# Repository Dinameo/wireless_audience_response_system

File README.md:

# Hệ thống trắc nghiệm tương tác sử dụng BLE và Wi-Fi

## Giới thiệu dự án

Dự án xây dựng hệ thống trắc nghiệm tương tác hỗ trợ tổ chức và theo dõi bài kiểm tra trong lớp học. Thay vì trả lời trực tiếp trên điện thoại hoặc máy tính, sinh viên có thể sử dụng thiết bị IoT với các nút A/B/C/D và SUBMIT để chọn rồi gửi đáp án. Giảng viên quản lý lớp học, danh sách sinh viên, câu hỏi và lượt thi trên giao diện web.

Hệ thống kết nối thiết bị theo hai cách: bo nRF52840 gửi dữ liệu BLE qua gateway chạy trên máy tính; bo ESP32 kết nối Wi-Fi và gửi dữ liệu đến API. Backend FastAPI xác thực thiết bị, tiếp nhận đáp án, lưu dữ liệu vào MySQL và cập nhật trạng thái bài thi để giảng viên theo dõi. Sau khi kết thúc, giảng viên có thể xem kết quả, thống kê và xuất bảng điểm.

Mục tiêu của dự án là kết hợp phần cứng IoT, giao tiếp không dây và phần mềm quản lý thành một quy trình trả lời trắc nghiệm liền mạch: từ tạo bài thi, ghép thiết bị với sinh viên, mở câu hỏi, nhận đáp án đến tổng hợp kết quả.

## Thành viên

| Họ và tên | MSSV |
|---|---:|
| Vũ Phạm Đức Văn | 23134064 |
| Phạm Đức Huy | 23134026 |
| Nguyễn Thiện Nhân | 23134041 |

Đề tài môn IoT, Khoa Cơ khí – Bộ môn Cơ điện tử, Trường Đại học Công nghệ Kỹ thuật TP. Hồ Chí Minh. Giảng viên hướng dẫn: TS. Bùi Hà Đức.

## Kiến trúc hệ thống

Hệ thống có hai lựa chọn thiết bị trả lời. nRF52840 gửi dữ liệu qua BLE tới gateway Python chạy trên laptop; ESP32 kết nối Wi-Fi và gọi API trực tiếp. Cả hai đường truyền đều đi tới FastAPI và MySQL. Trình duyệt giảng viên làm việc với web/API và nhận cập nhật qua WebSocket.

*nRF52840 dùng BLE gateway; ESP32 dùng Wi-Fi/HTTP trực tiếp tới server.*

## Chức năng chính

- Quản lý tài khoản giảng viên, môn học, lớp và danh sách sinh viên.
- Tạo bài thi, nhập câu hỏi từ DOCX/PDF có lớp văn bản và nhập danh sách từ Excel.
- Ghép thiết bị với sinh viên ở đầu mỗi lượt thi; danh sách ghép trong lượt thi là nguồn xác định chủ sở hữu đáp án.
- Trình chiếu câu hỏi, theo dõi trạng thái thiết bị, mở câu tiếp theo hoặc kết thúc bài thi.
- Từ chối đáp án của câu đã đóng, đáp án gửi trễ, nộp trùng hoặc thiết bị không thuộc lượt thi.
- Chấm điểm tối đa 10, xem thống kê và xuất bảng điểm cùng chi tiết câu trả lời ra Excel.

Theo báo cáo, cơ sở dữ liệu MySQL có 19 bảng cho tài khoản giảng viên, lớp/môn, sinh viên, lượt thi, câu hỏi, thiết bị, trạng thái kết nối và đáp án. Mỗi lượt thi chốt ghép thiết bị riêng; server ngăn dùng một thiết bị cho nhiều sinh viên trong cùng lượt và ngăn nộp lặp cho cùng câu.

## Luồng thiết bị nRF52840

Thiết bị có các nút A/B/C/D, nút SUBMIT, LED kết nối và LED gửi. Thiết bị quảng bá BLE; gateway nhận mã ID rồi hỏi server để xác thực. Khi server chấp nhận, gateway gửi ACCEPT. Lúc giảng viên mở câu, gateway gửi NEXT; người học chọn đáp án rồi nhấn SUBMIT để gửi ANS:X. Sau khi server lưu đáp án thành công, gateway gửi ACK. ACK xác nhận đã lưu, không báo đáp án đúng hay sai.

Mã firmware và mô tả state machine ở [NRF52840_Quiz_Remote_src/main/main.ino](NRF52840_Quiz_Remote_src/main/main.ino) và [README luồng firmware](NRF52840_Quiz_Remote_src/main/README.md). Mã gateway BLE cần chạy riêng trên máy có Bluetooth; gateway không nằm trong các tệp hiện có của repository.

## Giao diện web

Web cung cấp trang đăng nhập giảng viên và các chức năng quản lý lớp, thiết bị, bài thi và kết quả. Web và MySQL được triển khai bằng Docker Compose; FastAPI xử lý API và dữ liệu bài thi.

Xem cách chạy và cấu hình trong [web/README.md](web/README.md).

## Cấu trúc repository

- `web/`: giao diện giảng viên, FastAPI, API và cấu hình Docker Compose.
- `NRF52840_Quiz_Remote_src/main/`: firmware BLE cho thiết bị nRF52840 và tài liệu luồng hoạt động.
- `NRF52840_Quiz_Remote/`: sơ đồ nguyên lý, PCB KiCad và Gerber.
- `Case/`: các tệp thiết kế và STL liên quan đến vỏ thiết bị.
- `docs/images/`: ảnh kiến trúc, giao diện, luồng BLE và PCB trích từ báo cáo.

## Phần cứng

PCB nRF52840 được thiết kế hai lớp, có các đầu vào nút nhấn, hai LED trạng thái và LED nguồn. Báo cáo ghi kích thước thiết kế 66 × 152 mm, các nút chọn A/B/C/D và SUBMIT, cùng các thành phần nguồn và reset. Ảnh bên dưới đối chiếu mô hình PCB với ảnh bo đã gia công; ảnh chỉ ghi nhận một phần linh kiện đã lắp, không thay cho phép thử điện.

Ảnh đường mạch hai lớp F.Cu/B.Cu:

Báo cáo có mô tả quy trình thiết kế vỏ và một ảnh chi tiết vỏ in. Tuy nhiên báo cáo cũng nêu chưa có tệp SolidWorks/STL và chưa ghi nhận kiểm tra lắp ghép hoàn chỉnh; vì vậy phần vỏ vẫn cần được xác nhận thêm.

## Kiểm thử và giới hạn

Báo cáo ghi nhận một lượt thử nRF từ thao tác chọn C trên Serial đến ANS:C, nhận ACK và lưu lựa chọn C vào database. Báo cáo chưa có số liệu về độ trễ, tỷ lệ mất gói BLE hoặc kiểm thử tải với nhiều thiết bị cùng lúc.

Các lưu ý bảo mật được nêu trong báo cáo: BLE chưa có cơ chế chống giả mạo mạnh; ESP32 dùng HTTP trong mạng LAN và token thiết bị phải được giữ kín. Không đưa thông tin xác thực vào firmware công khai hoặc triển khai API trực tiếp lên Internet nếu chưa bổ sung bảo vệ phù hợp.

## Tài liệu

- [Báo cáo dự án (DOCX)](https://docs.google.com/document/d/1qnYOhXeeTpFeyJ0GafD6C87CJyP0sUIl/edit)
- [README hướng dẫn web](web/README.md)
- [README luồng firmware nRF52840](NRF52840_Quiz_Remote_src/main/README.md)

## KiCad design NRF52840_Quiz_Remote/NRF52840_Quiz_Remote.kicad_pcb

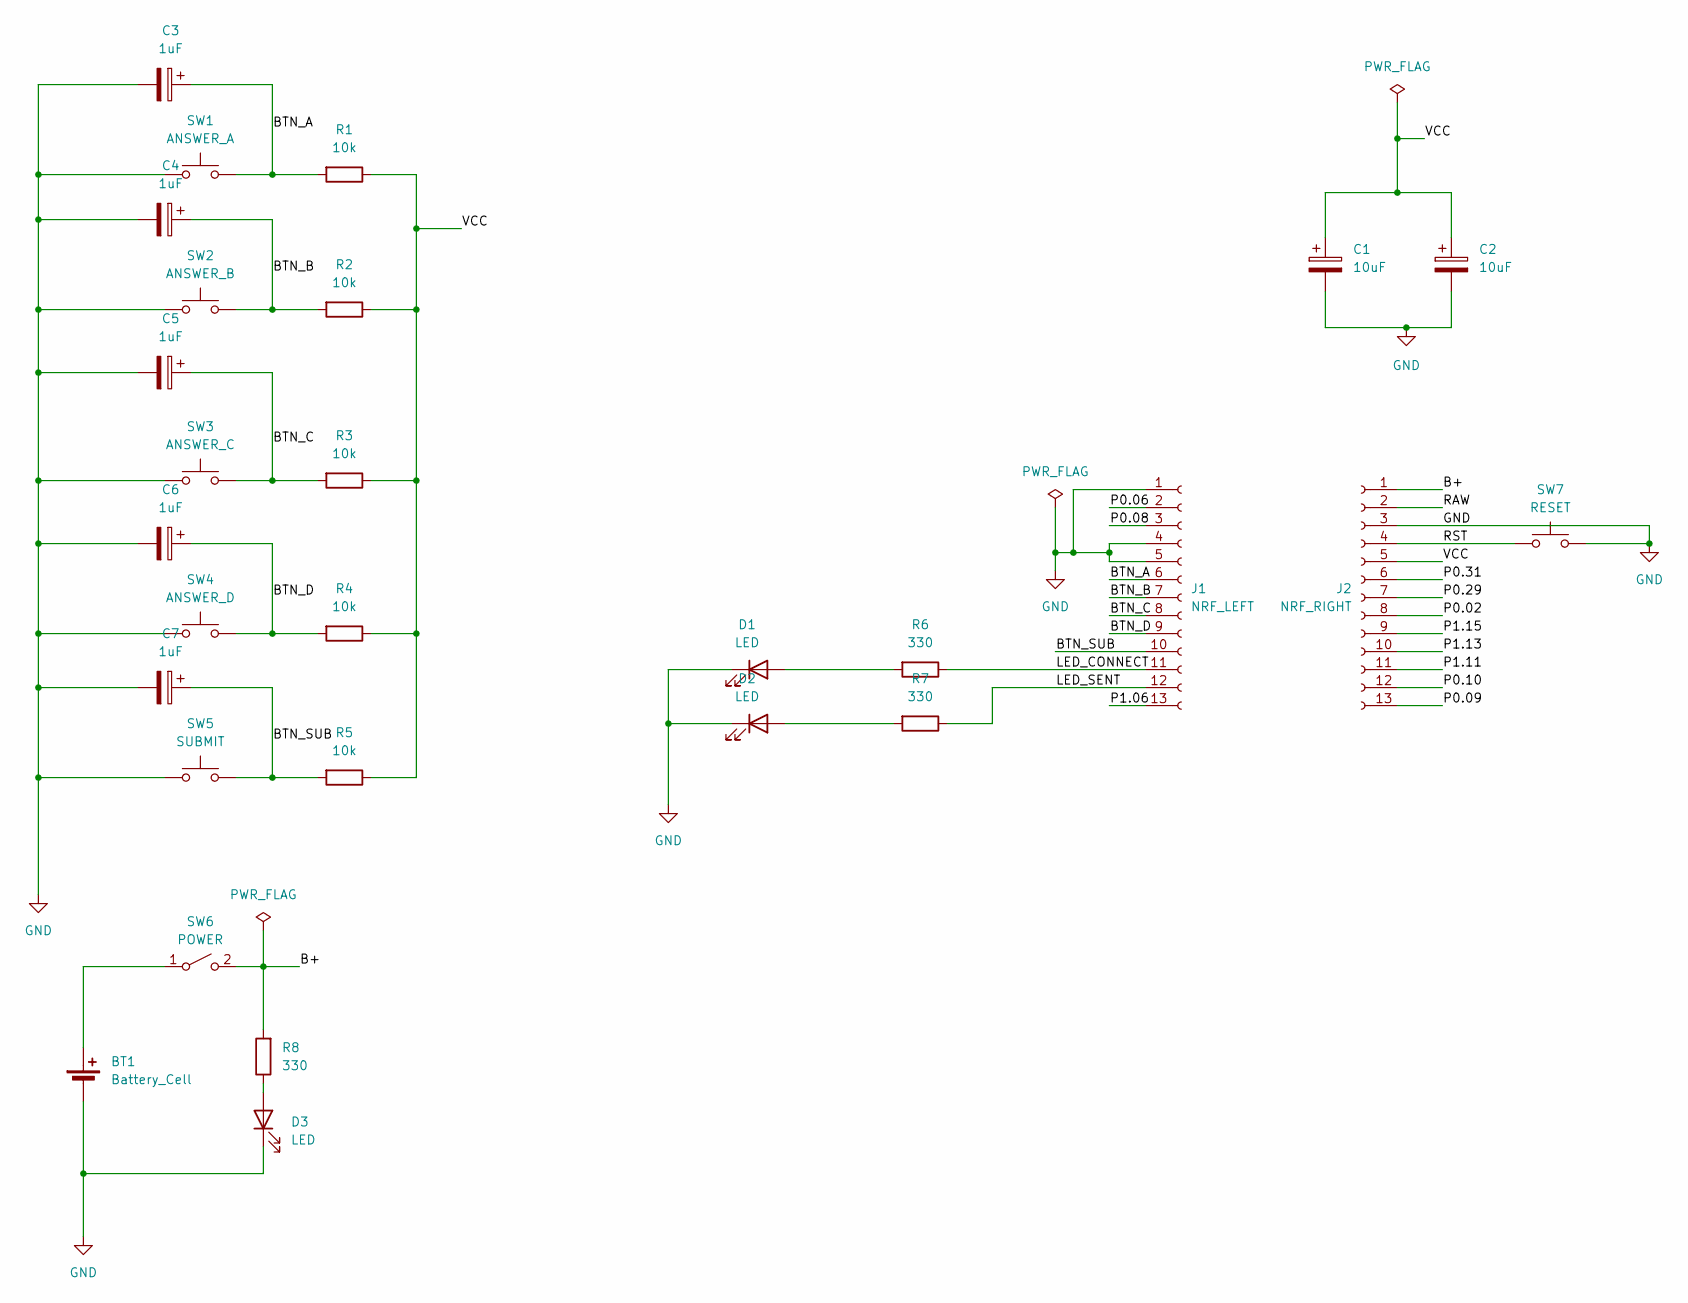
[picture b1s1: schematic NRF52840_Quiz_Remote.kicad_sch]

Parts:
BT1: Battery_Cell; Battery_Panasonic_CR2032-HFN_Horizontal_CircularHoles
C1, C2: 10uF; CP_Radial_D4.0mm_P2.00mm
C3, C4, C5, C6, C7: 1uF; CP_Radial_D5.0mm_P2.00mm
D1, D2, D3: LED; LED_D5.0mm
J1: NRF_LEFT; PinSocket_1x13_P2.54mm_Vertical
J2: NRF_RIGHT; PinSocket_1x13_P2.54mm_Vertical
R1, R2, R3, R4, R5: 10k; R_Axial_DIN0207_L6.3mm_D2.5mm_P7.62mm_Horizontal
R6, R7, R8: 330; R_Axial_DIN0207_L6.3mm_D2.5mm_P7.62mm_Horizontal
SW1: ANSWER_A; SW_PUSH_6mm_H4.3mm
SW2: ANSWER_B; SW_PUSH_6mm_H4.3mm
SW3: ANSWER_C; SW_PUSH_6mm_H4.3mm
SW4: ANSWER_D; SW_PUSH_6mm_H4.3mm
SW5: SUBMIT; SW_PUSH_6mm_H4.3mm
SW6: POWER; SS12D10_SPDT_v1
SW7: RESET; SW_PUSH_6mm_H4.3mm

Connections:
/B+: J2.1, R8.2, SW6.2 (B)
/BTN_A: C3.1, J1.6, R1.2, SW1.2
/BTN_B: C4.1, J1.7, R2.2, SW2.2
/BTN_C: C5.1, J1.8, R3.2, SW3.2
/BTN_D: C6.1, J1.9, R4.2, SW4.2
/BTN_SUB: C7.1, J1.10, R5.2, SW5.2
/LED_CONNECT: J1.11, R6.1
/LED_SENT: J1.12, R7.1
/P0.02: J2.8
/P0.06: J1.2
/P0.08: J1.3
/P0.09: J2.13
/P0.10: J2.12
/P0.29: J2.7
/P0.31: J2.6
/P1.06: J1.13
/P1.11: J2.11
/P1.13: J2.10
/P1.15: J2.9
/RAW: J2.2
/RST: J2.4, SW7.1
/VCC: C1.1, C2.1, J2.5, R1.1, R2.1, R3.1, R4.1, R5.1
GND: BT1.2 (-), C1.2, C2.2, C3.2, C4.2, C5.2, C6.2, C7.2, D1.1 (K), D2.1 (K), D3.1 (K), J1.1, J1.4, J1.5, J2.3, SW1.1, SW2.1, SW3.1, SW4.1, SW5.1, SW7.2
unnamed: BT1.1 (+), SW6.1 (A)
unnamed: D1.2 (A), R6.2
unnamed: D2.2 (A), R7.2
unnamed: D3.2 (A), R8.1

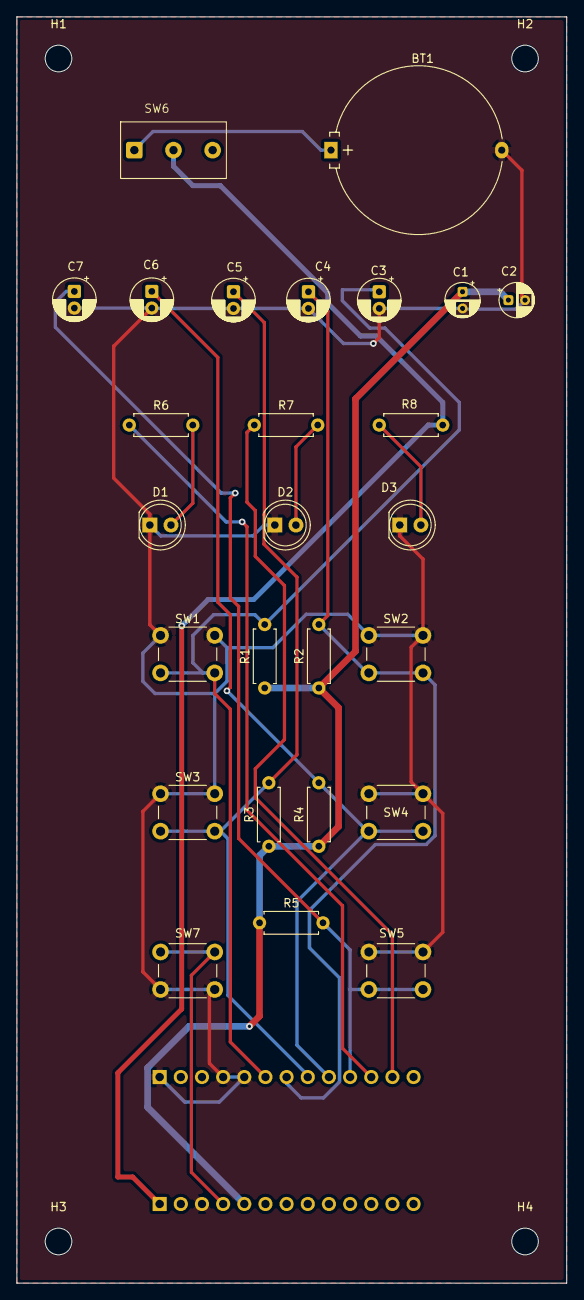
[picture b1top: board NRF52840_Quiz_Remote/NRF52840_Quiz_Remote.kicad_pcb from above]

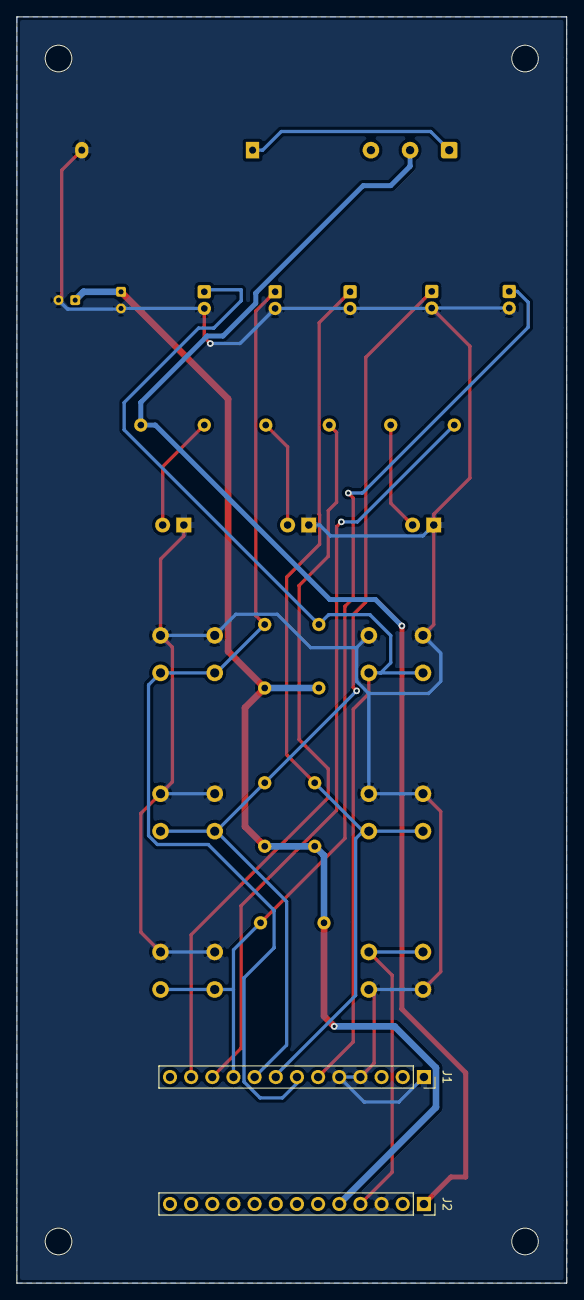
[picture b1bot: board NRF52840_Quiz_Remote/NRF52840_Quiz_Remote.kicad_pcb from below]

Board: 2 copper layers, 66.0 x 152.0 mm, 32 parts (2 on the bottom side), 15 nets.

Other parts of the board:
H1, H2, H3, H4: MountingHole_3.2mm_M3

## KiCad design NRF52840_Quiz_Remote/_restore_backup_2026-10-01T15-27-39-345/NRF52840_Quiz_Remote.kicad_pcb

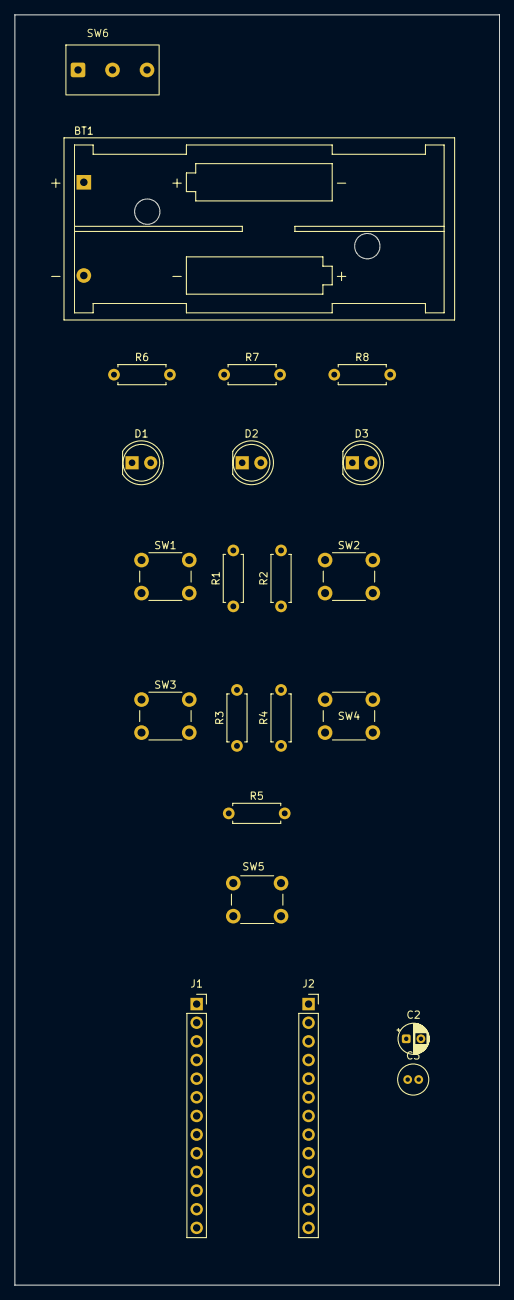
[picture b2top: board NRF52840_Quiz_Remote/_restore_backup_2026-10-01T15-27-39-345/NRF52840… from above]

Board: 2 copper layers, 66.0 x 173.0 mm, 22 parts (0 on the bottom side), 15 nets, no tracks yet.

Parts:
BT1: Battery; BatteryHolder_Keystone_2468_2xAAA
C2: 10uF; CP_Radial_D4.0mm_P2.00mm
C3: 100nF; C_Radial_D4.0mm_H5.0mm_P1.50mm
D1, D2, D3: LED; LED_D5.0mm
J1: NRF_LEFT; PinSocket_1x13_P2.54mm_Vertical
J2: NRF_RIGHT; PinSocket_1x13_P2.54mm_Vertical
R1, R2, R3, R4, R5: 10k; R_Axial_DIN0207_L6.3mm_D2.5mm_P7.62mm_Horizontal
R6, R7, R8: 330; R_Axial_DIN0207_L6.3mm_D2.5mm_P7.62mm_Horizontal
SW1: ANSWER_A; SW_PUSH_6mm_H4.3mm
SW2: ANSWER_B; SW_PUSH_6mm_H4.3mm
SW3: ANSWER_C; SW_PUSH_6mm_H4.3mm
SW4: ANSWER_D; SW_PUSH_6mm_H4.3mm
SW5: SUBMIT; SW_PUSH_6mm_H4.3mm
SW6: POWER; SS12D10_SPDT_v1

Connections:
/B+: J1.1, J2.1, SW6.2 (B)
/BTN_A: J1.6, R1.2, SW1.2
/BTN_B: J1.7, R2.2, SW2.2
/BTN_C: J1.8, R3.2, SW3.2
/BTN_D: J1.9, R4.2, SW4.2
/BTN_SUB: J1.10, R5.2, SW5.2
/LED_CONNECT: J1.11, R6.1
/LED_NGUON: J1.13, R8.1
/LED_SENT: J1.12, R7.1
/VCC: C2.1, C3.1, J2.5, R1.1, R2.1, R3.1, R4.1, R5.1
GND: BT1.2 (-), C2.2, C3.2, D1.1 (K), D2.1 (K), D3.1 (K), J1.4, J1.5, J2.3, SW1.1, SW2.1, SW3.1, SW4.1, SW5.1
unnamed: BT1.1 (+), SW6.1 (A)
unnamed: D1.2 (A), R6.2
unnamed: D2.2 (A), R7.2
unnamed: D3.2 (A), R8.2
